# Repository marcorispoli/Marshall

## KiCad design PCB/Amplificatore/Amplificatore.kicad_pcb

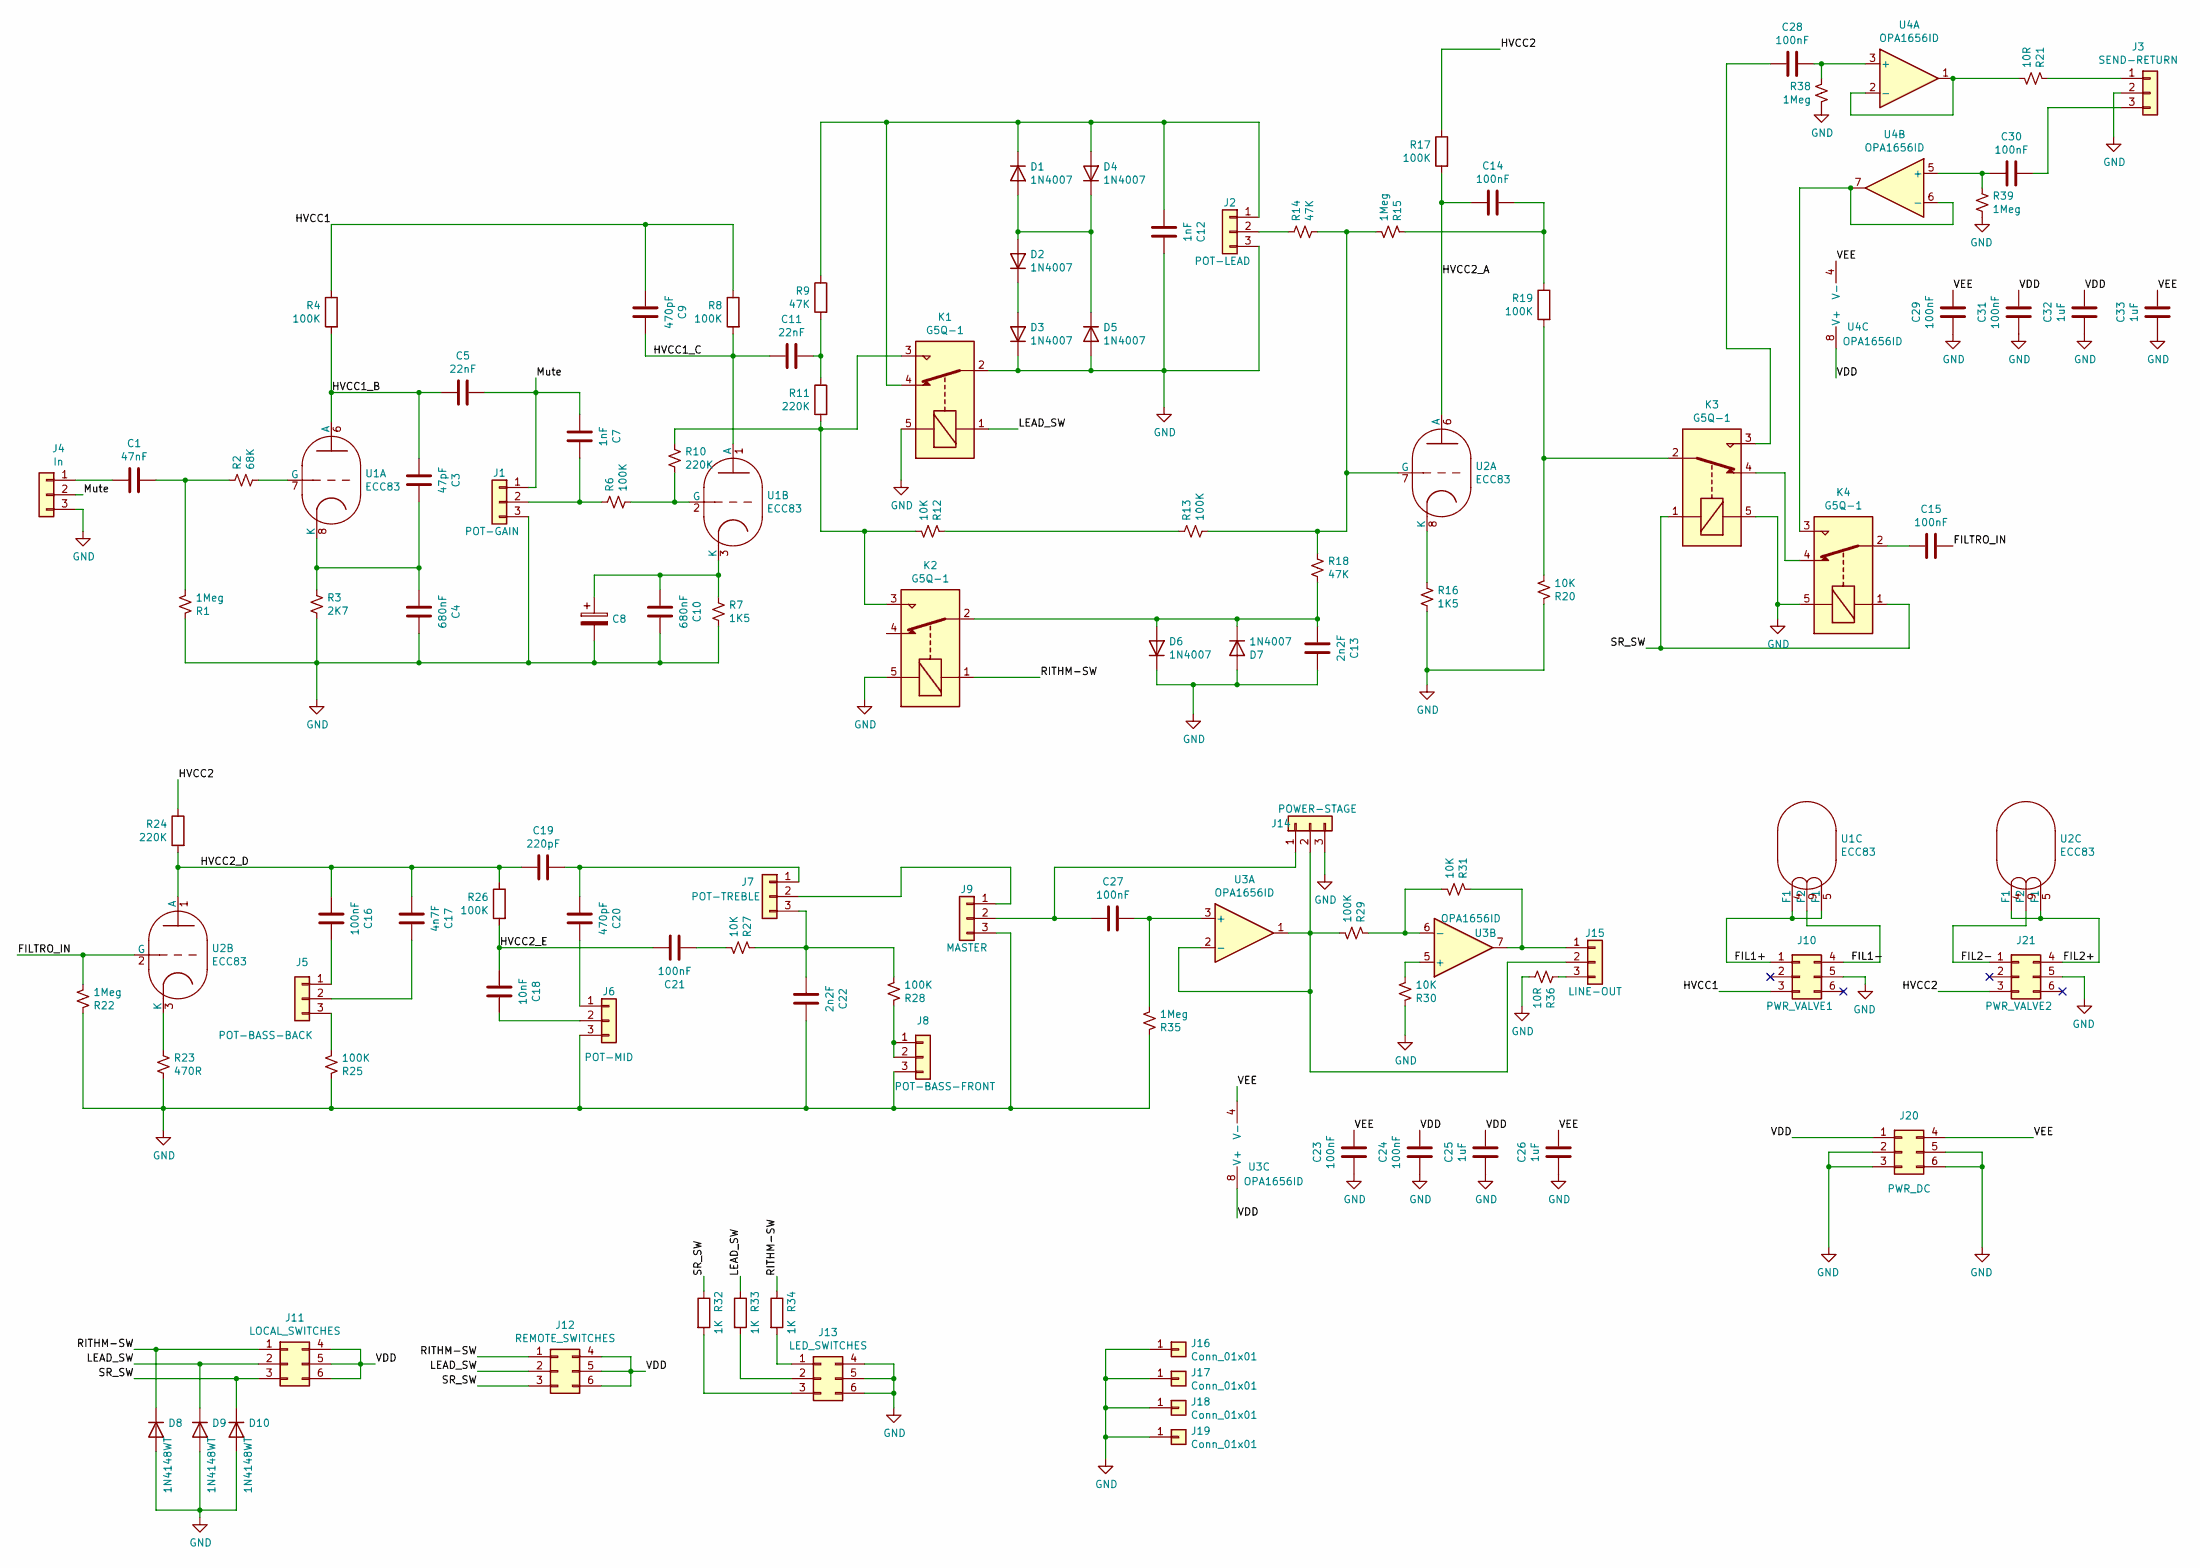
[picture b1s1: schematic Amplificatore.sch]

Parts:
C1: 47nF; C_Rect_L4.6mm_W3.0mm_P2.50mm_MKS02_FKP02
C3: 47pF; C_Rect_L7.2mm_W4.5mm_P5.00mm_FKS2_FKP2_MKS2_MKP2
C4, C10: 680nF; C_Rect_L18.0mm_W11.0mm_P15.00mm_FKS3_FKP3
C5, C11: 22nF; C_Rect_L13.0mm_W4.0mm_P10.00mm_FKS3_FKP3_MKS4
C7, C12: 1nF; C_Rect_L13.0mm_W4.0mm_P10.00mm_FKS3_FKP3_MKS4
C8: 10uF; CP_EIA-3216-10_Kemet-I
C9, C20: 470pF; C_Rect_L10.0mm_W3.0mm_P7.50mm_MKS4
C13, C22: 2n2F; C_Rect_L13.0mm_W4.0mm_P10.00mm_FKS3_FKP3_MKS4
C14, C15, C16, C21, C27, C28, C30: 100nF; C_Rect_L18.0mm_W5.0mm_P15.00mm_FKS3_FKP3
C17: 4n7F; C_Rect_L13.0mm_W4.0mm_P10.00mm_FKS3_FKP3_MKS4
C18: 10nF; C_Rect_L13.0mm_W4.0mm_P10.00mm_FKS3_FKP3_MKS4
C19: 220pF; C_Rect_L7.2mm_W4.5mm_P5.00mm_FKS2_FKP2_MKS2_MKP2
C23, C24, C29, C31: 100nF; C_0805_2012Metric_Pad1.18x1.45mm_HandSolder
C25, C26, C32, C33: 1uF; C_1206_3216Metric_Pad1.33x1.80mm_HandSolder
D1, D2, D3, D4, D5, D6, D7: 1N4007; D_DO-41_SOD81_P10.16mm_Horizontal
D8, D9, D10: 1N4148WT; D_SOD-523
J1: POT-GAIN; PinSocket_1x03_P2.00mm_Vertical
J2: POT-LEAD; PinSocket_1x03_P2.00mm_Vertical
J3: SEND-RETURN; PinSocket_1x03_P2.00mm_Vertical
J4: In; PinSocket_1x03_P2.00mm_Vertical
J5: POT-BASS-BACK; PinSocket_1x03_P2.00mm_Vertical
J6: POT-MID; PinSocket_1x03_P2.00mm_Vertical
J7: POT-TREBLE; PinSocket_1x03_P2.00mm_Vertical
J8: POT-BASS-FRONT; PinSocket_1x03_P2.00mm_Vertical
J9: MASTER; PinSocket_1x03_P2.00mm_Vertical
J10: PWR_VALVE1; Molex_Micro-Fit_3.0_43045-0612_2x03_P3.00mm_Vertical
J11: LOCAL_SWITCHES; Molex_Micro-Fit_3.0_43045-0612_2x03_P3.00mm_Vertical
J12: REMOTE_SWITCHES; Molex_Micro-Fit_3.0_43045-0612_2x03_P3.00mm_Vertical
J13: LED_SWITCHES; Molex_Micro-Fit_3.0_43045-0612_2x03_P3.00mm_Vertical
J14: POWER-STAGE; PinSocket_1x03_P2.00mm_Vertical
J15: LINE-OUT; PinSocket_1x03_P2.00mm_Vertical
J16, J17, J18, J19: Conn_01x01; MountingHole_3.2mm_M3_DIN965_Pad_TopBottom
J20: PWR_DC; Molex_Micro-Fit_3.0_43045-0612_2x03_P3.00mm_Vertical
J21: PWR_VALVE2; Molex_Micro-Fit_3.0_43045-0612_2x03_P3.00mm_Vertical
K1, K2, K3, K4: G5Q-1; Relay_SPDT_Omron-G5Q-1
R1, R15, R22, R35, R38, R39: 1Meg; R_0805_2012Metric
R2: 68K; R_0805_2012Metric
R3: 2K7; R_0805_2012Metric
R4, R8, R17, R19, R26: 100K; R_2512_6332Metric
R6, R13, R25, R28, R29: 100K; R_0805_2012Metric
R7, R16: 1K5; R_0805_2012Metric
R9: 47K; R_2512_6332Metric
R10: 220K; R_0805_2012Metric
R11, R24: 220K; R_2512_6332Metric
R12, R20, R27, R30, R31: 10K; R_0805_2012Metric
R14, R18: 47K; R_0805_2012Metric
R21, R36: 10R; R_0805_2012Metric
R23: 470R; R_0805_2012Metric
R32, R33, R34: 1K; R_2512_6332Metric
U1, U2: ECC83; Valve_ECC-83-3
U3, U4: OPA1656ID; SO-8_3.9x4.9mm_P1.27mm

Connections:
/FIL1+: J10.1, U1.4 (F1), U1.5 (F1)
/FIL1-: J10.4, U1.9 (F2)
/FIL2+: J21.4, U2.4 (F1), U2.5 (F1)
/FIL2-: J21.1, U2.9 (F2)
/FILTRO_IN: C15.1, R22.2, U2.2 (G)
/HVCC1: C9.2, J10.3, R4.1, R8.1
/HVCC1_B: C3.2, C5.2, R4.2, U1.6 (A)
/HVCC1_C: C9.1, C11.2, R8.2, U1.1 (A)
/HVCC2: J21.3, R17.1, R24.1
/HVCC2_A: C14.2, R17.2, U2.6 (A)
/HVCC2_D: C16.2, C17.2, C19.2, R24.2, R26.1, U2.1 (A)
/HVCC2_E: C18.2, C21.1, R26.2
/LEAD_SW: D9.1 (K), J11.2, J12.2, K1.1, R33.1
/Mute: C5.1, C7.2, J1.1, J4.2
/RITHM-SW: D8.1 (K), J11.1, J12.1, K2.1, R34.1
/SR_SW: D10.1 (K), J11.3, J12.3, K3.1, K4.1, R32.1
/VDD: C24.1, C25.1, C31.1, C32.1, J11.4, J11.5, J11.6, J12.4, J12.5, J12.6, J20.1, U3.8 (V+), U4.8 (V+)
/VEE: C23.1, C26.1, C29.1, C33.1, J20.4, U3.4 (V-), U4.4 (V-)
GND: C4.1, C8.2, C10.1, C12.1, C13.1, C22.1, C23.2, C24.2, C25.2, C26.2, C29.2, C31.2, C32.2, C33.2, D3.1 (K), D5.2 (A), D6.1 (K), D7.2 (A), D8.2 (A), D9.2 (A), D10.2 (A), J1.3, J2.3, J3.2, J4.3, J6.3, J8.3, J9.3, J10.5, J13.4, J13.5, J13.6, J14.3, J16.1, J17.1, J18.1, J19.1, J20.2, J20.3, J20.5, J20.6, J21.5, K1.2, K1.5, K2.5, K3.5, K4.5, R1.1, R3.2, R7.2, R16.2, R20.1, R22.1, R23.2, R25.1, R30.1, R35.1, R36.2, R38.2, R39.2
unnamed: C1.1, R1.2, R2.1
unnamed: C1.2, J4.1
unnamed: C3.1, C4.2, R3.1, U1.8 (K)
unnamed: C7.1, J1.2, R6.1
unnamed: C8.1, C10.2, R7.1, U1.3 (K)
unnamed: C11.1, R9.2, R11.1
unnamed: C12.2, D1.1 (K), D4.2 (A), J2.1, K1.4, R9.1
unnamed: C13.2, D6.2 (A), D7.1 (K), K2.2, R18.2
unnamed: C14.1, R15.1, R19.1
unnamed: C15.2, K4.2
unnamed: C16.1, J5.1
unnamed: C17.1, J5.2
unnamed: C18.1, J6.2
unnamed: C19.1, C20.2, J7.1
unnamed: C20.1, J6.1
unnamed: C21.2, R27.2
unnamed: C22.2, J7.3, R27.1, R28.2
unnamed: C27.1, J9.2, J14.1
unnamed: C27.2, R35.2, U3.3 (+)
unnamed: C28.1, R38.1, U4.3 (+)
unnamed: C28.2, K3.3
unnamed: C30.1, R39.1, U4.5 (+)
unnamed: C30.2, J3.3
unnamed: D1.2 (A), D2.2 (A), D4.1 (K), D5.1 (K)
unnamed: D2.1 (K), D3.2 (A)
unnamed: J2.2, R14.1
unnamed: J3.1, R21.1
unnamed: J5.3, R25.2
unnamed: J7.2, J9.1
unnamed: J8.1, J8.2, R28.1
unnamed: J13.1, R34.2
unnamed: J13.2, R33.2
unnamed: J13.3, R32.2
unnamed: J14.2, J15.2, R29.2, U3.1, U3.2 (-)
unnamed: J15.1, R31.1, U3.7
unnamed: J15.3, R36.1
unnamed: K1.3, K2.3, R10.1, R11.2, R12.2
unnamed: K3.2, R19.2, R20.2
unnamed: K3.4, K4.4
unnamed: K4.3, U4.6 (-), U4.7
unnamed: R2.2, U1.7 (G)
unnamed: R6.2, R10.2, U1.2 (G)
unnamed: R12.1, R13.1
unnamed: R13.2, R14.2, R15.2, R18.1, U2.7 (G)
unnamed: R16.1, U2.8 (K)
unnamed: R21.2, U4.1, U4.2 (-)
unnamed: R23.1, U2.3 (K)
unnamed: R29.1, R31.2, U3.6 (-)
unnamed: R30.2, U3.5 (+)

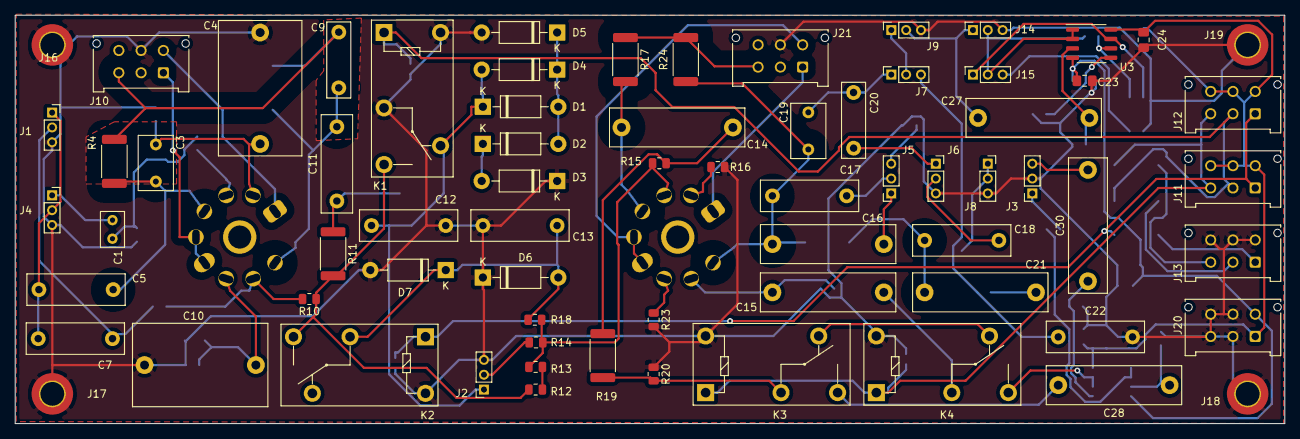
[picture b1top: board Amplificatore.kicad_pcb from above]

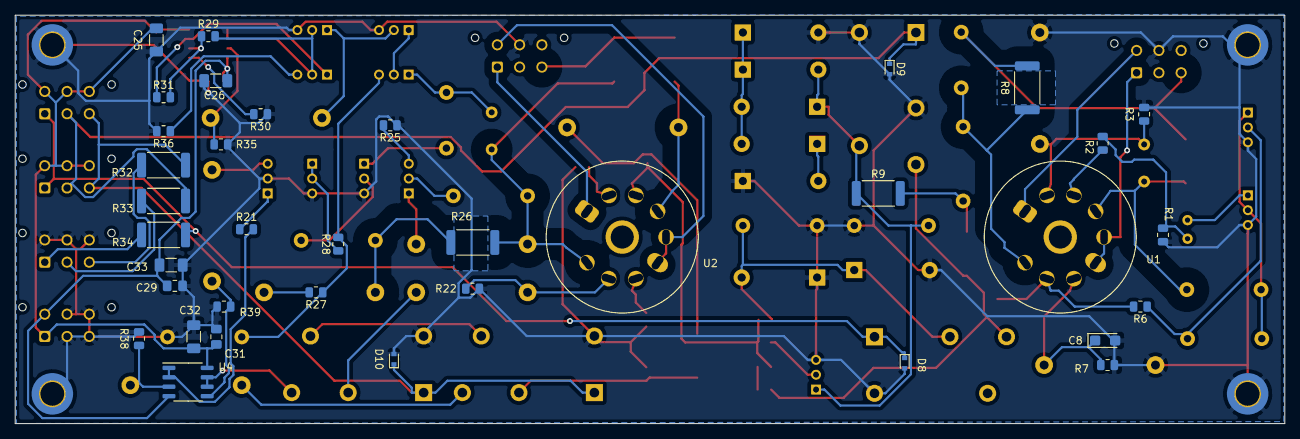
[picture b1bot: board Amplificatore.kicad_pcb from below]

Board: 2 copper layers, 171.0 x 55.0 mm, 107 parts (36 on the bottom side), 68 nets.

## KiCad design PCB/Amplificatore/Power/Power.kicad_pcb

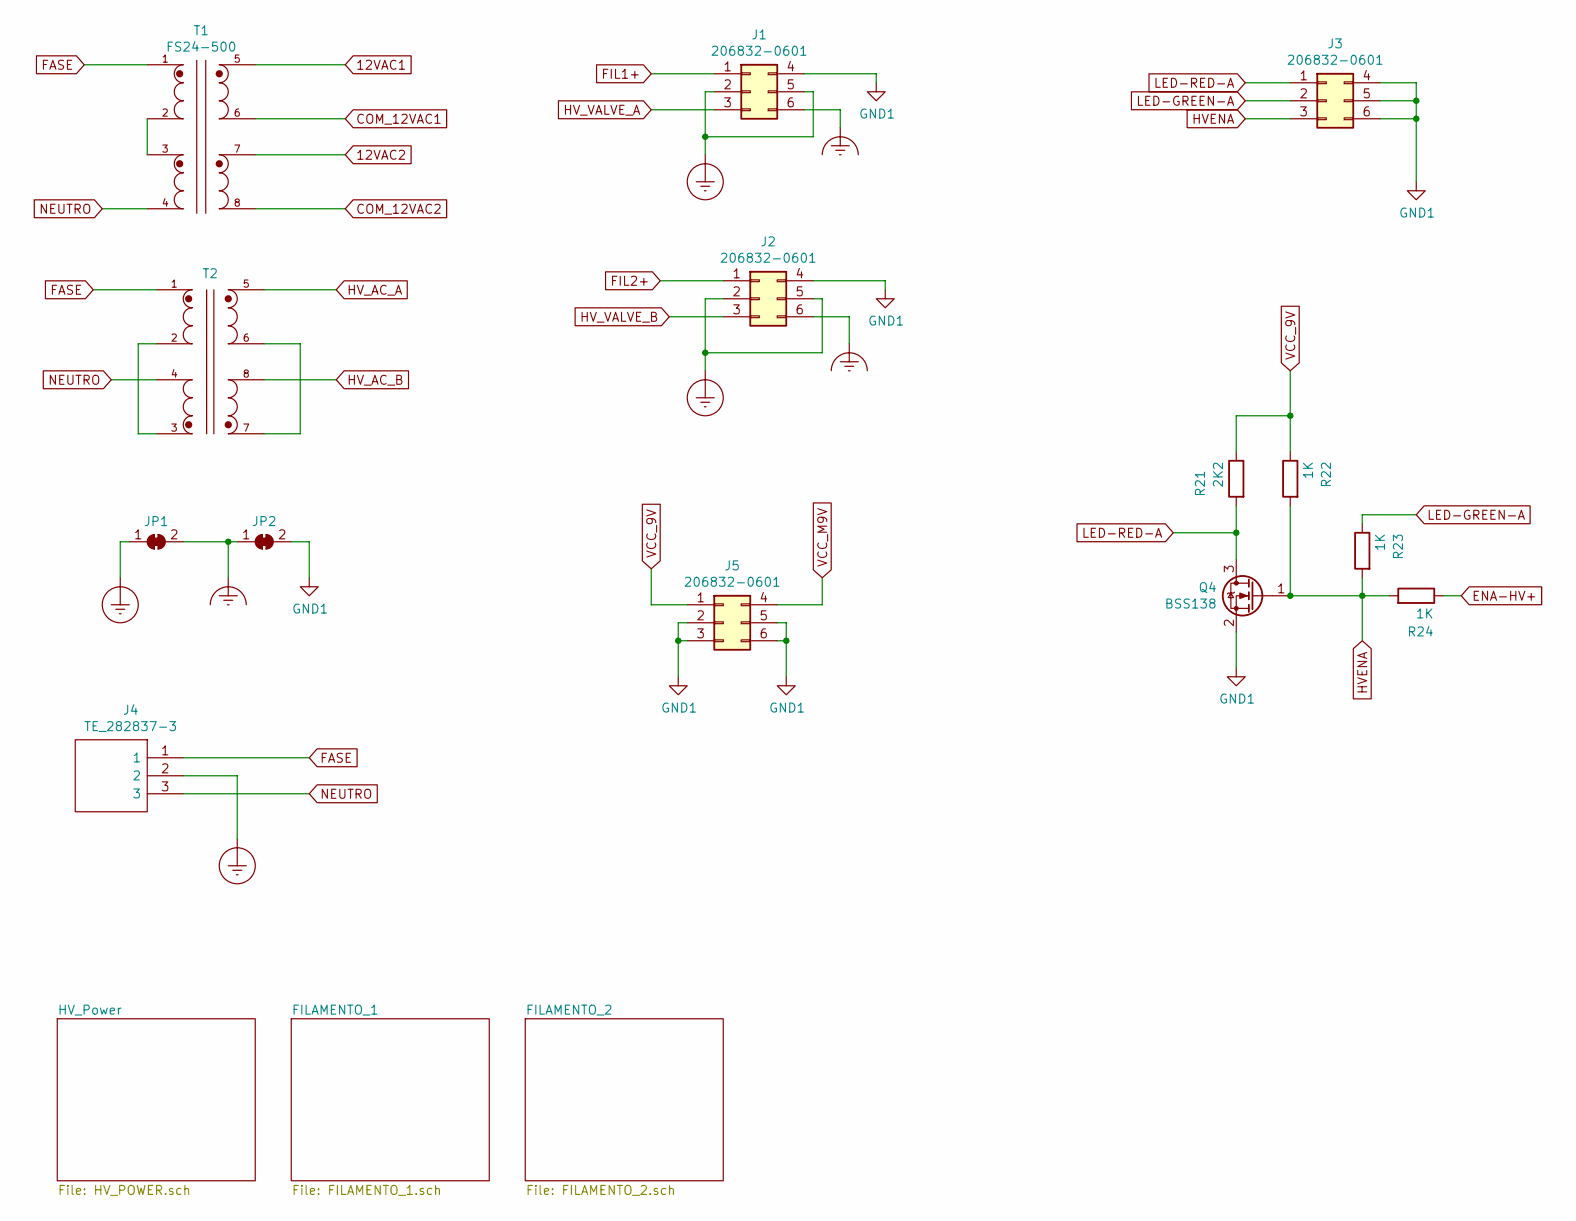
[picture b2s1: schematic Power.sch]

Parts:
J1, J2, J3, J5: Molex_MicroFit_2x3; Molex_Micro-Fit_3.0_43045-0612_2x03_P3.00mm_Vertical
J4: TE_282837-3
JP1, JP2: SolderJumper_2_Bridged; SolderJumper-2_P1.3mm_Bridged2Bar_Pad1.0x1.5mm
Q4: BSS138; SOT-23
R21: 2K2; R_0805_2012Metric_Pad1.20x1.40mm_HandSolder
R22, R23, R24: 1K; R_0805_2012Metric_Pad1.20x1.40mm_HandSolder
T1: FS24-500; TRANSFORMER_FS24-500
T2: Transformer_FP230-25; XFMR_FP230-25

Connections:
12VAC1: T1.5; also elsewhere on the board
12VAC2: T1.7; also elsewhere on the board
COM_12VAC1: T1.6; also elsewhere on the board
COM_12VAC2: T1.8; also elsewhere on the board
ENA-HV+: R24.1; also elsewhere on the board
Earth_Clean: J1.6, J2.6, JP1.2 (B), JP2.1 (A); also elsewhere on the board
Earth_Protective: J1.2, J1.5, J2.2, J2.5, J4.2, JP1.1 (A)
FASE: J4.1, T1.1, T2.1
FIL1+: J1.1; also elsewhere on the board
FIL2+: J2.1; also elsewhere on the board
GND1: J1.4, J2.4, J3.4, J3.5, J3.6, J5.2, J5.3, J5.5, J5.6, JP2.2 (B), Q4.2 (S); also elsewhere on the board
HVENA: J3.3, Q4.1 (G), R22.2, R23.2, R24.2
HV_AC_A: T2.5; also elsewhere on the board
HV_AC_B: T2.8; also elsewhere on the board
HV_VALVE_A: J1.3; also elsewhere on the board
HV_VALVE_B: J2.3; also elsewhere on the board
LED-GREEN-A: J3.2, R23.1
LED-RED-A: J3.1, Q4.3 (D), R21.2
NEUTRO: J4.3, T1.4, T2.4
unnamed: T1.2, T1.3
unnamed: T2.2, T2.3
unnamed: T2.6, T2.7
VCC_9V: J5.1, R21.1, R22.1; also elsewhere on the board
VCC_M9V: J5.4; also elsewhere on the board

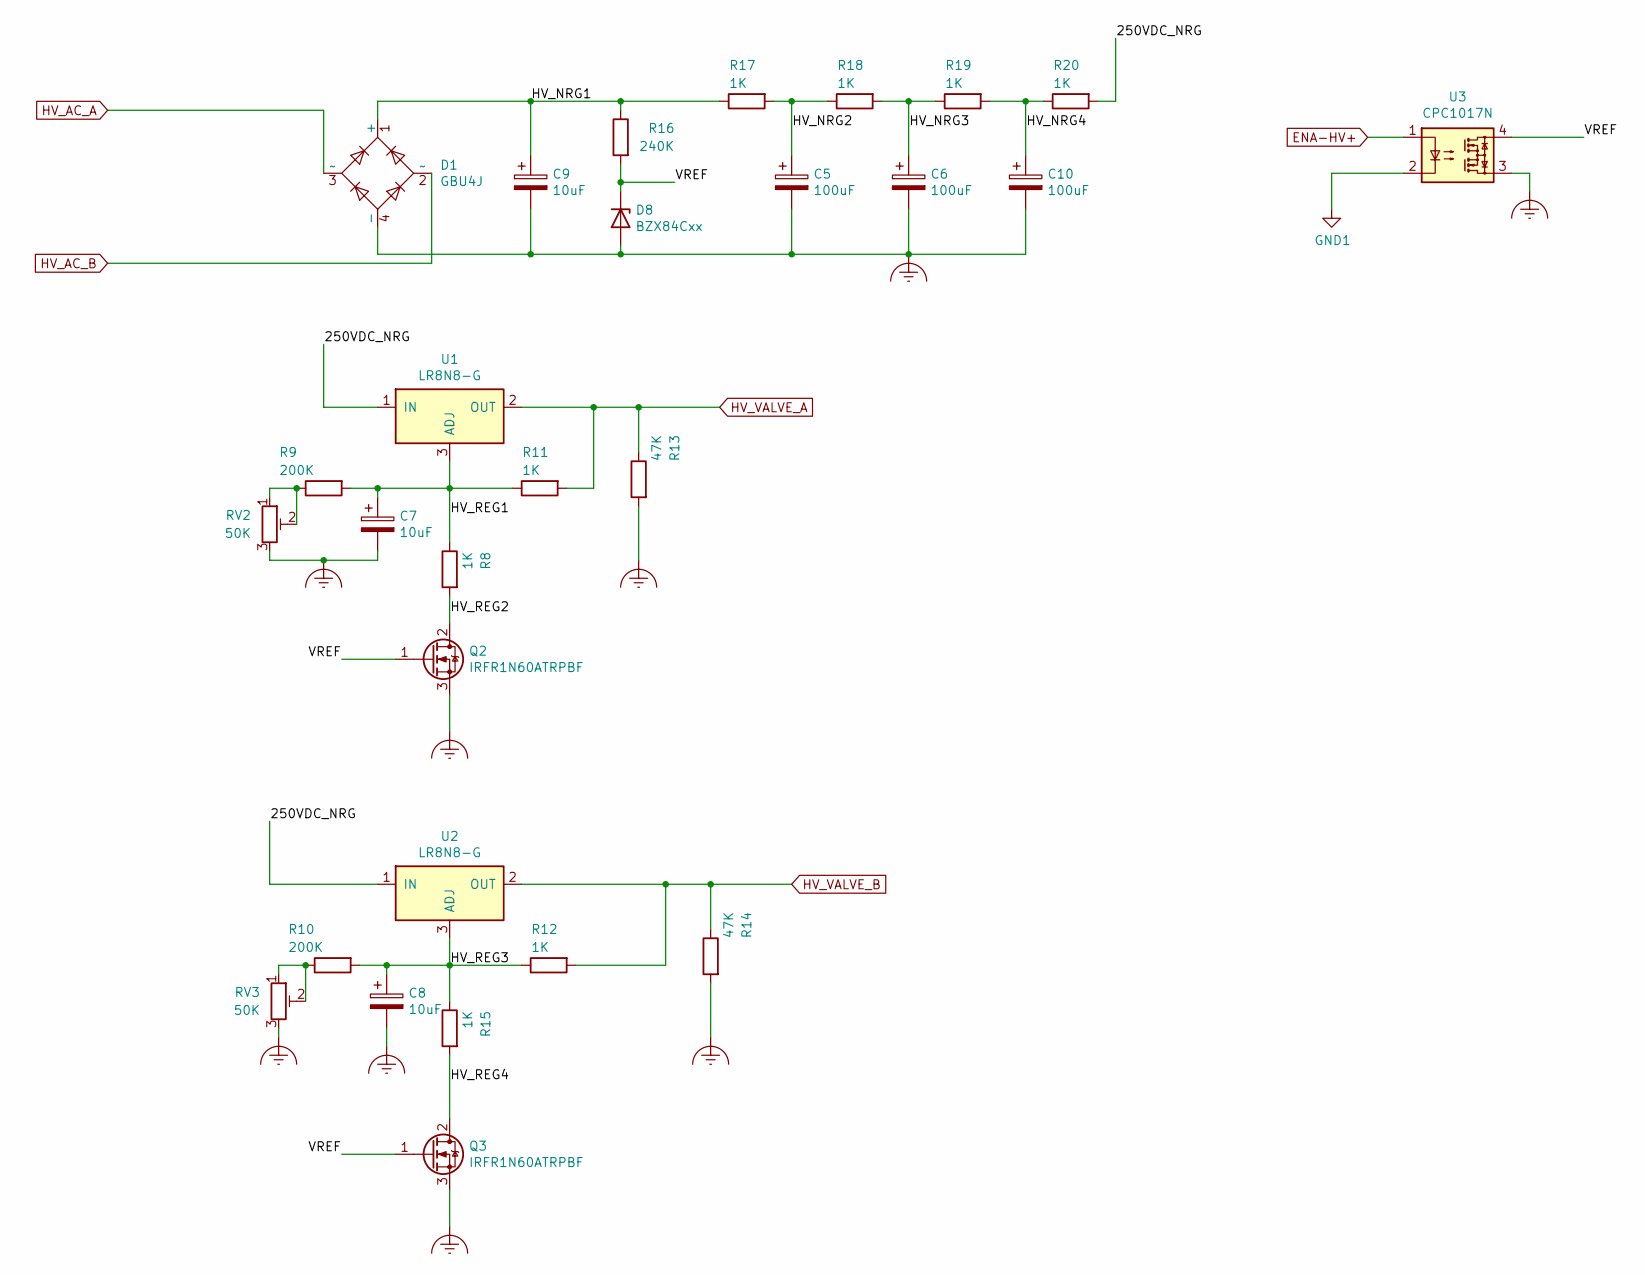
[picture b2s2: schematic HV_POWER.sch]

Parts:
C5, C6, C10: 100uF; CP_Radial_D18.0mm_P7.50mm
C7, C8, C9: 10uF; CP_Radial_D10.0mm_P5.00mm
D1: GBU4J; Diode_Bridge_Vishay_GBU
D8: BZX84Cxx; D_SOT-23_ANK
Q2, Q3: IRFR1N60ATRPBF; TO-252-2
R8, R11, R12, R15, R17, R18, R19, R20: 1K; R_2512_6332Metric_Pad1.40x3.35mm_HandSolder
R9, R10: 200K; R_2512_6332Metric_Pad1.40x3.35mm_HandSolder
R13, R14: 47K; R_2512_6332Metric_Pad1.40x3.35mm_HandSolder
R16: 240K; R_2512_6332Metric_Pad1.40x3.35mm_HandSolder
RV2, RV3: 50K; Potentiometer_Bourns_3314G_Vertical
U1, U2: LR8N8-G; SOT-89-3
U3: CPC1017N; SOP-4_3.8x4.1mm_P2.54mm

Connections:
/HV_Power/250VDC_NRG: R20.2, U1.1 (IN), U2.1 (IN)
/HV_Power/HV_NRG1: C9.1, D1.1 (+), R16.1, R17.1
/HV_Power/HV_NRG2: C5.1, R17.2, R18.1
/HV_Power/HV_NRG3: C6.1, R18.2, R19.1
/HV_Power/HV_NRG4: C10.1, R19.2, R20.1
/HV_Power/HV_REG1: C7.1, R8.1, R9.2, R11.1, U1.3 (ADJ)
/HV_Power/HV_REG2: Q2.2 (D), R8.2
/HV_Power/HV_REG3: C8.1, R10.2, R12.1, R15.1, U2.3 (ADJ)
/HV_Power/HV_REG4: Q3.2 (D), R15.2
/HV_Power/VREF: D8.1 (K), Q2.1 (G), Q3.1 (G), R16.2, U3.4
ENA-HV+: U3.1; also elsewhere on the board
Earth_Clean: C5.2, C6.2, C7.2, C8.2, C9.2, C10.2, D1.4 (-), D8.2 (A), Q2.3 (S), Q3.3 (S), R13.2, R14.2, RV2.3, RV3.3, U3.3; also elsewhere on the board
GND1: U3.2; also elsewhere on the board
HV_AC_A: D1.3 (~~); also elsewhere on the board
HV_AC_B: D1.2 (~~); also elsewhere on the board
HV_VALVE_A: R11.2, R13.1, U1.2 (OUT); also elsewhere on the board
HV_VALVE_B: R12.2, R14.1, U2.2 (OUT); also elsewhere on the board
unnamed: R9.1, RV2.1, RV2.2
unnamed: R10.1, RV3.1, RV3.2

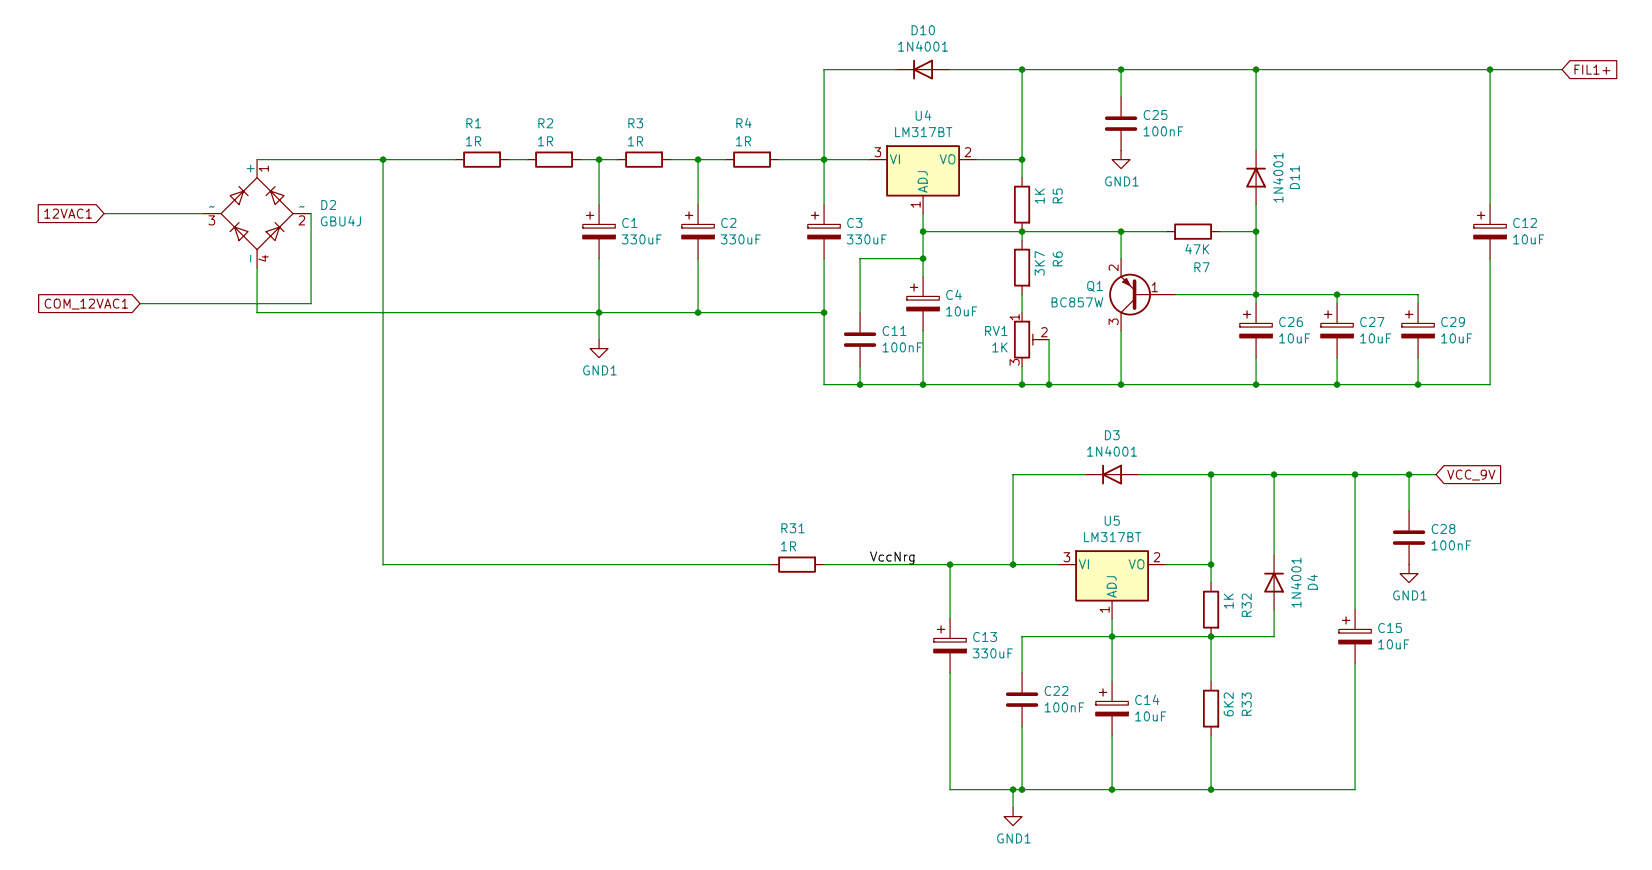
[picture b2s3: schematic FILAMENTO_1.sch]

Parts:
C1, C2, C3, C13: 330uF; CP_Radial_D8.0mm_P3.50mm
C4, C12, C14, C15, C26, C27, C29: 10uF; CP_Radial_D5.0mm_P2.00mm
C11, C22, C25, C28: 100nF; C_0805_2012Metric_Pad1.18x1.45mm_HandSolder
D2: GBU4J; Diode_Bridge_Vishay_GBU
D3, D4, D10, D11: 1N4001; D_DO-41_SOD81_P12.70mm_Horizontal
Q1: BC857W; SOT-323_SC-70
R1, R2, R3, R4, R31: 1R; R_2512_6332Metric_Pad1.40x3.35mm_HandSolder
R5, R32: 1K; R_0805_2012Metric_Pad1.20x1.40mm_HandSolder
R6: 3K7; R_0805_2012Metric_Pad1.20x1.40mm_HandSolder
R7: 47K; R_0805_2012Metric_Pad1.20x1.40mm_HandSolder
R33: 6K2; R_0805_2012Metric_Pad1.20x1.40mm_HandSolder
RV1: 1K; Potenziometro_Serie_35_35WR100KLFTR
U4, U5: LM317BT; TO-220-3_Horizontal_TabDown

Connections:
12VAC1: D2.3 (~~); also elsewhere on the board
/FILAMENTO_1/VccNrg: C13.1, D3.1 (K), R31.2, U5.3 (VI)
COM_12VAC1: D2.2 (~~); also elsewhere on the board
FIL1+: C12.1, C25.1, D10.2 (A), D11.1 (K), R5.1, U4.2 (VO); also elsewhere on the board
GND1: C1.2, C2.2, C3.2, C4.2, C11.2, C12.2, C13.2, C14.2, C15.2, C22.2, C25.2, C26.2, C27.2, C28.2, C29.2, D2.4 (-), Q1.3 (C), R33.2, RV1.2, RV1.3; also elsewhere on the board
unnamed: C1.1, R2.2, R3.1
unnamed: C2.1, R3.2, R4.1
unnamed: C3.1, D10.1 (K), R4.2, U4.3 (VI)
unnamed: C4.1, C11.1, Q1.2 (E), R5.2, R6.1, R7.2, U4.1 (ADJ)
unnamed: C14.1, C22.1, D4.2 (A), R32.2, R33.1, U5.1 (ADJ)
unnamed: C26.1, C27.1, C29.1, D11.2 (A), Q1.1 (B), R7.1
unnamed: D2.1 (+), R1.1, R31.1
unnamed: R1.2, R2.1
unnamed: R6.2, RV1.1
VCC_9V: C15.1, C28.1, D3.2 (A), D4.1 (K), R32.1, U5.2 (VO); also elsewhere on the board

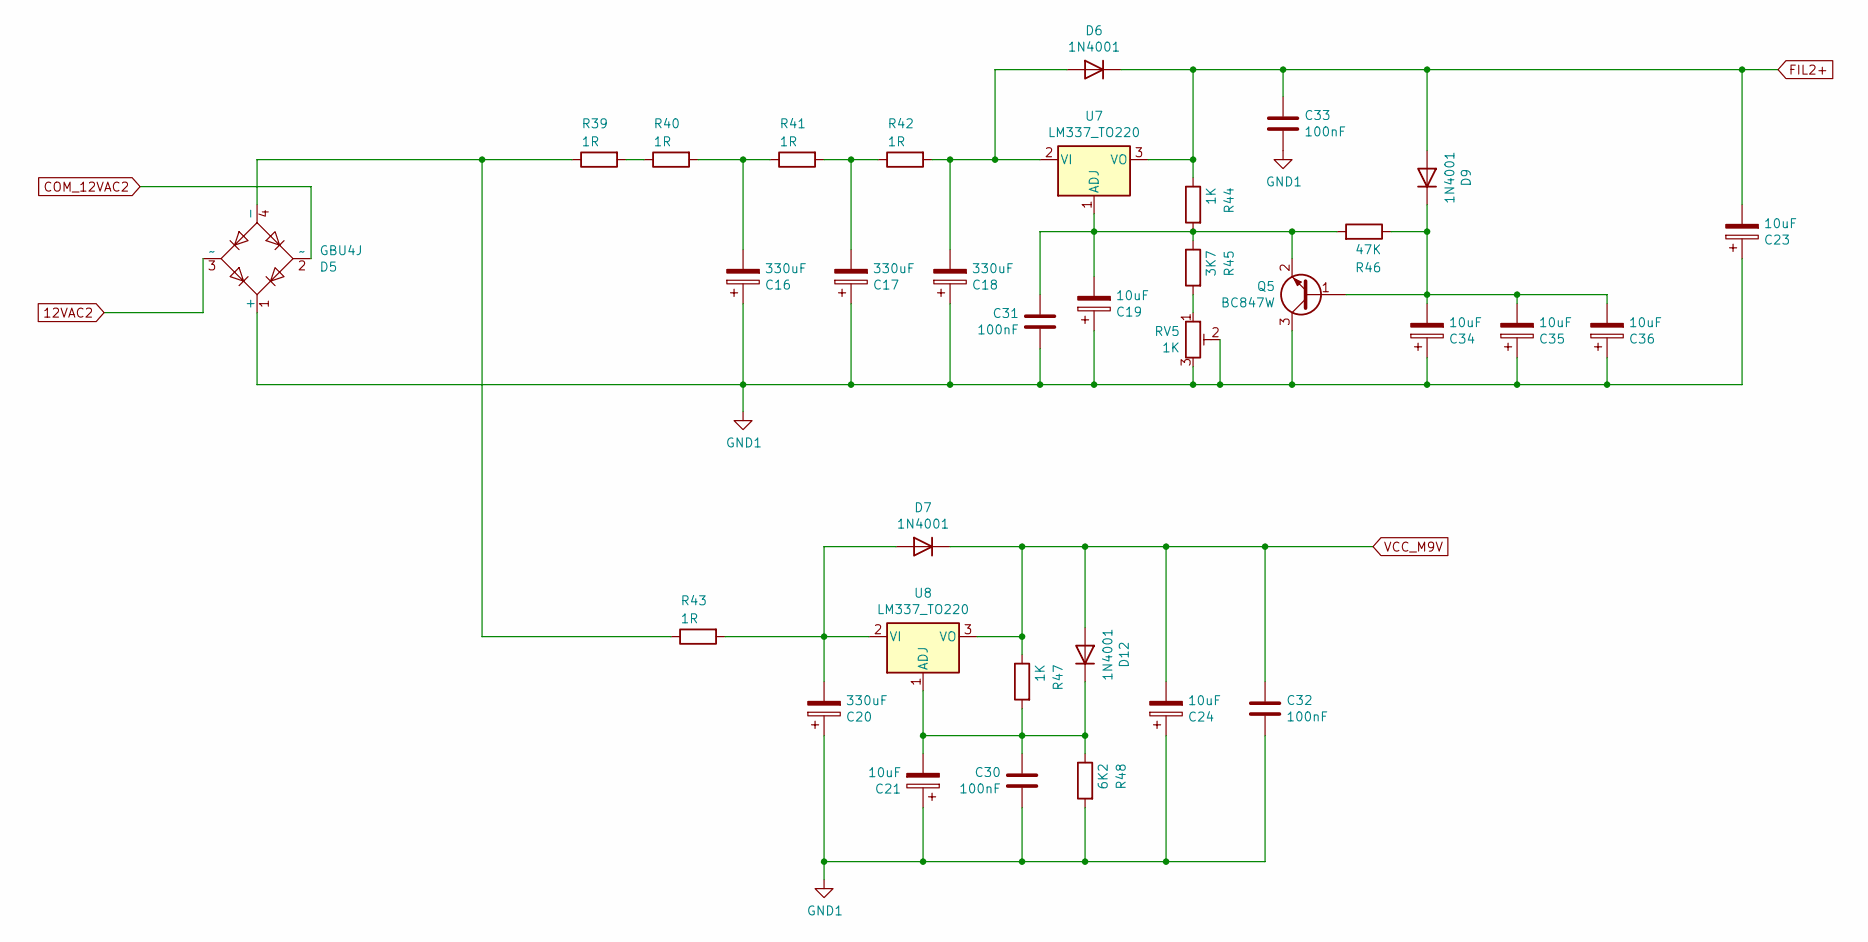
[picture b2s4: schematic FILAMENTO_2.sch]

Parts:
C16, C17, C18, C20: 330uF; CP_Radial_D8.0mm_P3.50mm
C19, C21, C23, C24, C34, C35, C36: 10uF; CP_Radial_D5.0mm_P2.00mm
C30, C31, C32, C33: 100nF; C_0805_2012Metric_Pad1.18x1.45mm_HandSolder
D5: GBU4J; Diode_Bridge_Vishay_GBU
D6, D7, D9, D12: 1N4001; D_DO-41_SOD81_P12.70mm_Horizontal
Q5: BC847W; SOT-323_SC-70
R39, R40, R41, R42, R43: 1R; R_2512_6332Metric_Pad1.40x3.35mm_HandSolder
R44, R47: 1K; R_0805_2012Metric_Pad1.20x1.40mm_HandSolder
R45: 3K7; R_0805_2012Metric_Pad1.20x1.40mm_HandSolder
R46: 47K; R_0805_2012Metric_Pad1.20x1.40mm_HandSolder
R48: 6K2; R_0805_2012Metric_Pad1.20x1.40mm_HandSolder
RV5: 1K; Potenziometro_Serie_35_35WR100KLFTR
U7, U8: LM337_TO220; TO-220-3_Vertical

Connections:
12VAC2: D5.3 (~~); also elsewhere on the board
COM_12VAC2: D5.2 (~~); also elsewhere on the board
FIL2+: C23.2, C33.1, D6.1 (K), D9.2 (A), R44.1, U7.3 (VO); also elsewhere on the board
GND1: C16.1, C17.1, C18.1, C19.1, C20.1, C21.1, C23.1, C24.1, C30.1, C31.1, C32.2, C33.2, C34.1, C35.1, C36.1, D5.1 (+), Q5.3 (C), R48.2, RV5.2, RV5.3; also elsewhere on the board
unnamed: C16.2, R40.2, R41.1
unnamed: C17.2, R41.2, R42.1
unnamed: C18.2, D6.2 (A), R42.2, U7.2 (VI)
unnamed: C19.2, C31.2, Q5.2 (E), R44.2, R45.1, R46.2, U7.1 (ADJ)
unnamed: C20.2, D7.2 (A), R43.2, U8.2 (VI)
unnamed: C21.2, C30.2, D12.1 (K), R47.2, R48.1, U8.1 (ADJ)
unnamed: C34.2, C35.2, C36.2, D9.1 (K), Q5.1 (B), R46.1
unnamed: D5.4 (-), R39.1, R43.1
unnamed: R39.2, R40.1
unnamed: R45.2, RV5.1
VCC_M9V: C24.2, C32.1, D7.1 (K), D12.2 (A), R47.1, U8.3 (VO); also elsewhere on the board

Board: 2 copper layers, 110 parts (14 on the bottom side), 56 nets, no tracks yet.

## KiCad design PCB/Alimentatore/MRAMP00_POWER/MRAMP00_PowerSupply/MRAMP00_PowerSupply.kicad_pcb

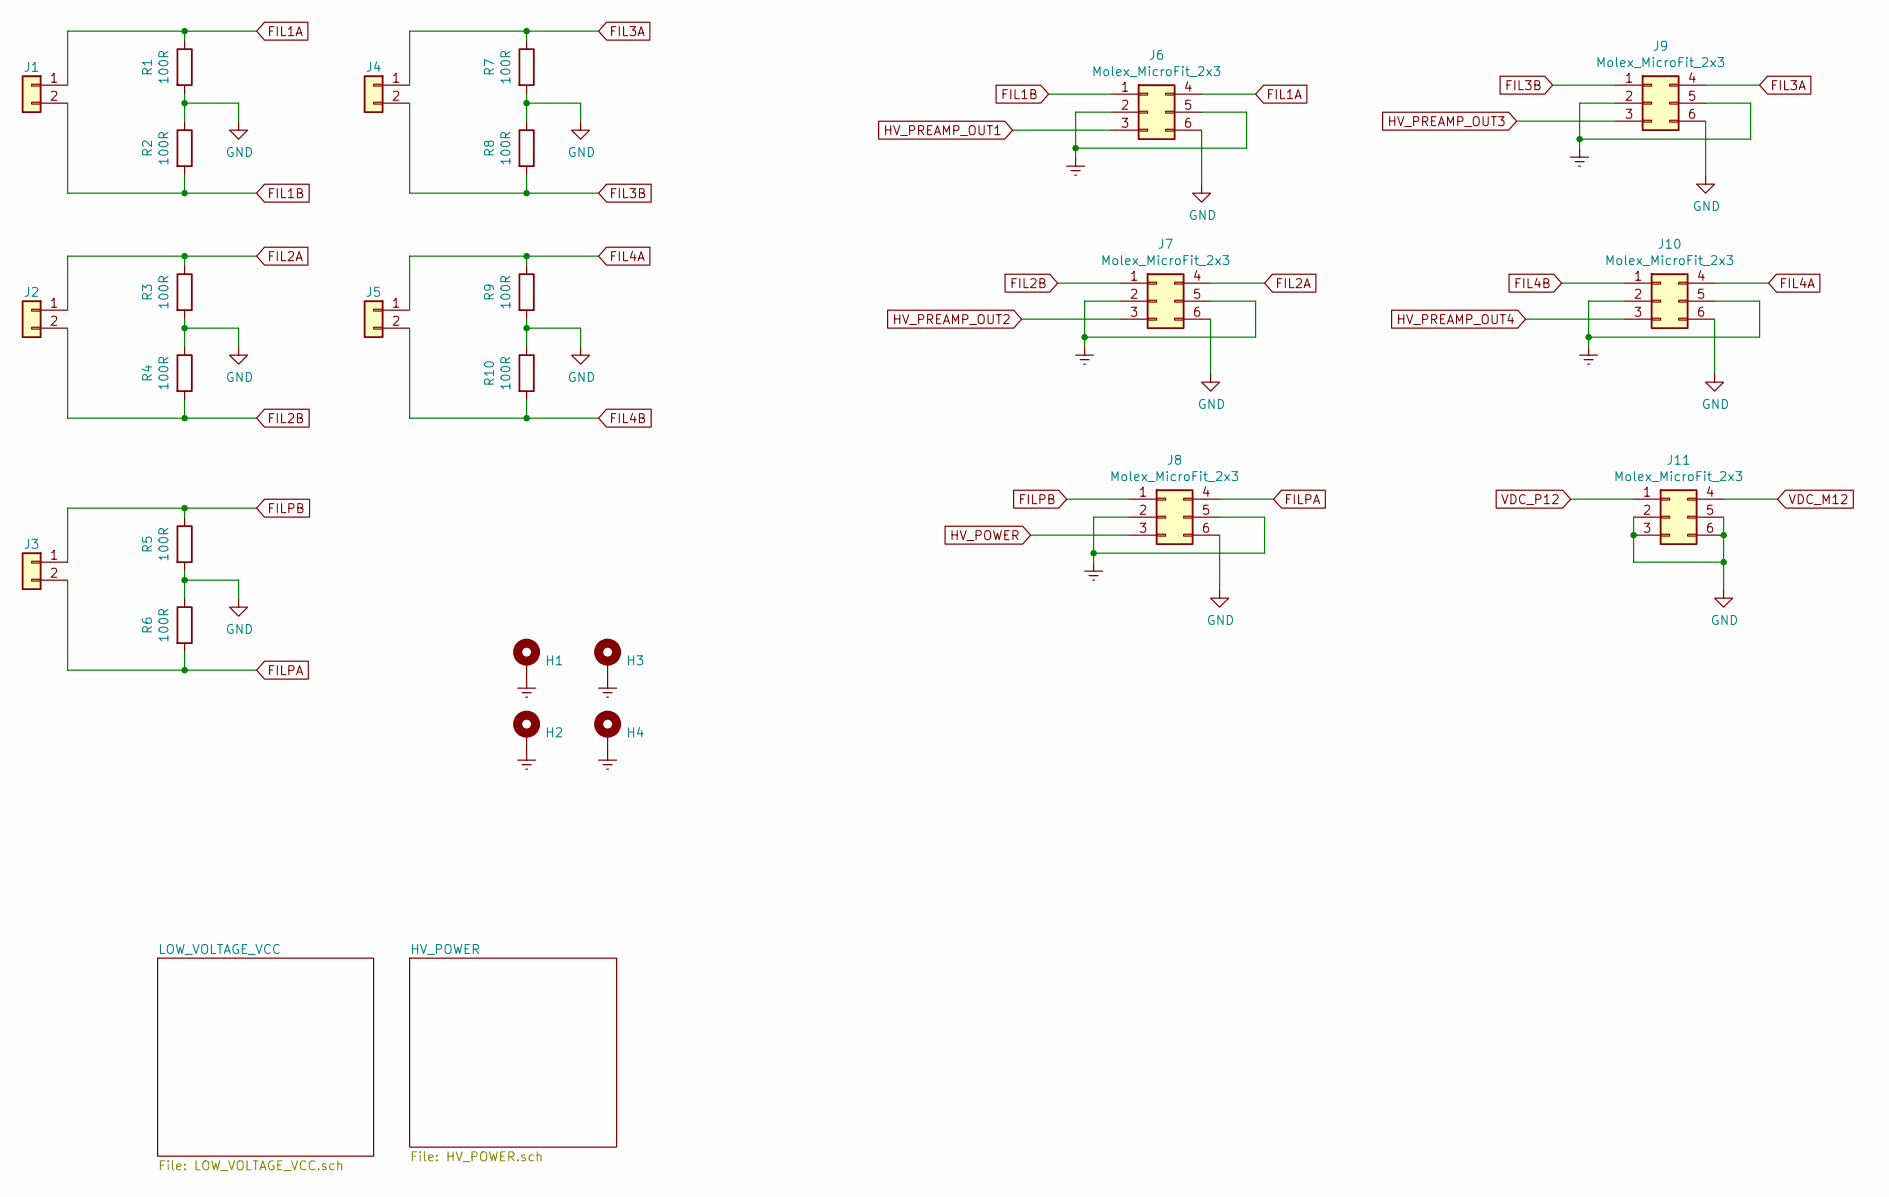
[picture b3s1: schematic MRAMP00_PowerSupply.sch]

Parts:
H1, H2, H3, H4: MountingHole_Pad; MountingHole_3.2mm_M3_Pad
J1, J2, J3, J4, J5: Conn_01x04; PhoenixContact_GMSTBVA_2,5_2-G_1x02_P7.50mm_Vertical
J6, J7, J8, J9, J10, J11: Molex_MicroFit_2x3; Molex_Micro-Fit_3.0_43045-0612_2x03_P3.00mm_Vertical
R1, R2, R3, R4, R5, R6, R7, R8, R9, R10: 100R; R_1206_3216Metric_Pad1.30x1.75mm_HandSolder

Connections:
Earth: H1.1, H2.1, H3.1, H4.1, J6.2, J6.5, J7.2, J7.5, J8.2, J8.5, J9.2, J9.5, J10.2, J10.5; also elsewhere on the board
FIL1A: J1.1, J6.4, R1.1
FIL1B: J1.2, J6.1, R2.2
FIL2A: J2.1, J7.4, R3.1
FIL2B: J2.2, J7.1, R4.2
FIL3A: J4.1, J9.4, R7.1
FIL3B: J4.2, J9.1, R8.2
FIL4A: J5.1, J10.4, R9.1
FIL4B: J5.2, J10.1, R10.2
FILPA: J3.2, J8.4, R6.2
FILPB: J3.1, J8.1, R5.1
GND: J6.6, J7.6, J8.6, J9.6, J10.6, J11.2, J11.3, J11.5, J11.6, R1.2, R2.1, R3.2, R4.1, R5.2, R6.1, R7.2, R8.1, R9.2, R10.1; also elsewhere on the board
HV_POWER: J8.3; also elsewhere on the board
HV_PREAMP_OUT1: J6.3; also elsewhere on the board
HV_PREAMP_OUT2: J7.3; also elsewhere on the board
HV_PREAMP_OUT3: J9.3; also elsewhere on the board
HV_PREAMP_OUT4: J10.3; also elsewhere on the board
VDC_M12: J11.4; also elsewhere on the board
VDC_P12: J11.1; also elsewhere on the board
